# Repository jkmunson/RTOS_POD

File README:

BEGINNING OF NOTES BY WYATT:
3/10/2024

* TFT display guide: https://www.youtube.com/watch?v=3qnB5gsp8eE&t=2s
* SD card guide: https://01001000.xyz/2020-08-09-Tutorial-STM32CubeIDE-SD-card/
* All the SPI and GPIO pin assignments are made in the .ioc file.
* SCK, MISO, and MOSI are automaticly assigned by the SPI enabled in the .ioc
* ^ but CS, RESET, and DC need to be assigned manually.
* The ili9341.h file and main.h file will need to reflect the .ioc file pin assignments. 
* I used stack size = 512 for the display/SD thread. Testing lower values has caused a fault in the past.
* Will need to change the "startup file" from f4xxxx to whichever board we are using.
* None of the display's touch screen pins are used (i.e. T_IRQ1, T_DO, T_DIN, T_CS, T_CLK)

I was on an f4xxx board, but I used the following SPI/GPIOs for the SD/Display:
SD:
	SCK		->	PB10
	MISO	->	PC2
	MOSI	->	PC1
	CS		->	PC3
DISPLAY:
	SD0 (MISO)	->	n/a (specify master only transmit in .ioc)
	LED			->	+3.3V
	SCK			->	PA5
	SDI	(MOSI)	->	PA7
	DC			->	PB1
	RESET		->	PB0
	CS			->	PA4
	VCC			->  +5V
	
I uploaded my wyatt.c and wyatt.h code, but it doesn't look like main.c is configured for FreeRTOS to run.
Once it is, ADD THE FOLLOWING CODE AS ITS OWN THREAD:
  
*   HOW THE FSM WORKS:
	The display initializes by showing the names of the files on the SD card, and blinking to show which file is currently hovered over.
	Change boolean variables "sel_next" and "sel_prev" to highlight files other than the one currently highlighted.
	change boolean variable "readFile" to open the file that's currently hovered over and access its contents.
	change boolean variable "viewDirectory" to close the file you're reading and view the list of file names again.
	
	changing "readFile" while already reading a file does nothing.
	changing "viewDirectory" while already viewing the directory does nothing.
	
END OF NOTES BY WYATT.

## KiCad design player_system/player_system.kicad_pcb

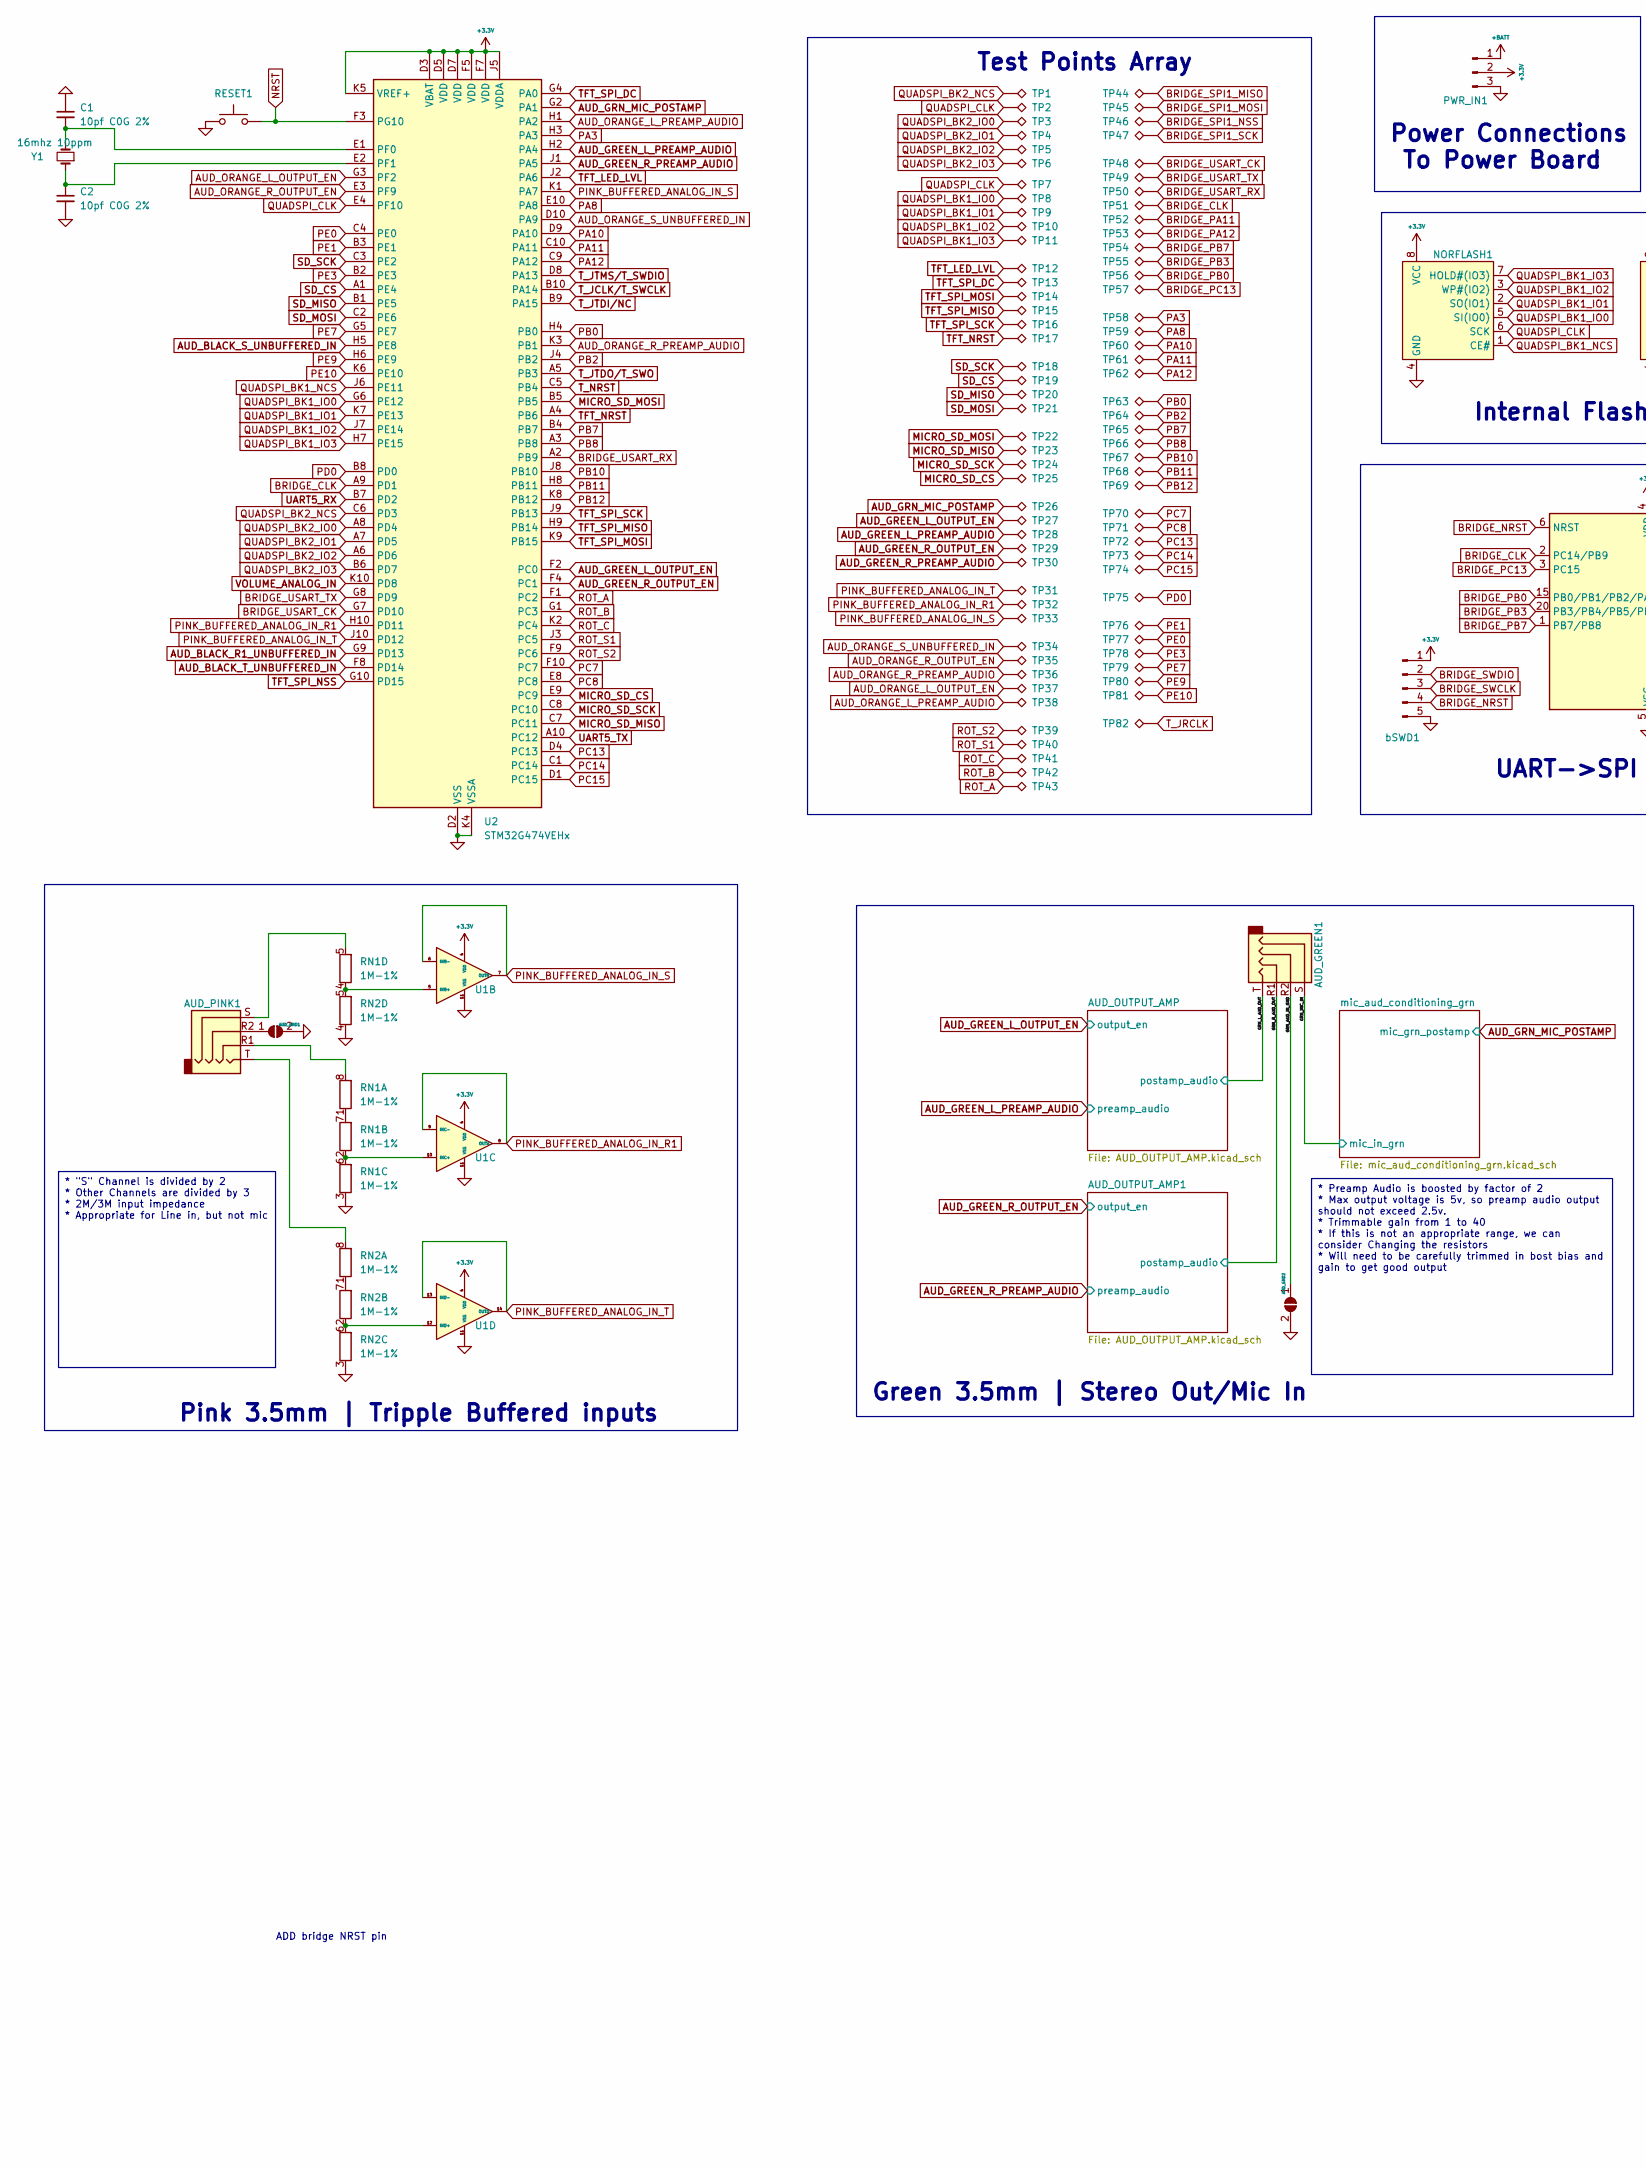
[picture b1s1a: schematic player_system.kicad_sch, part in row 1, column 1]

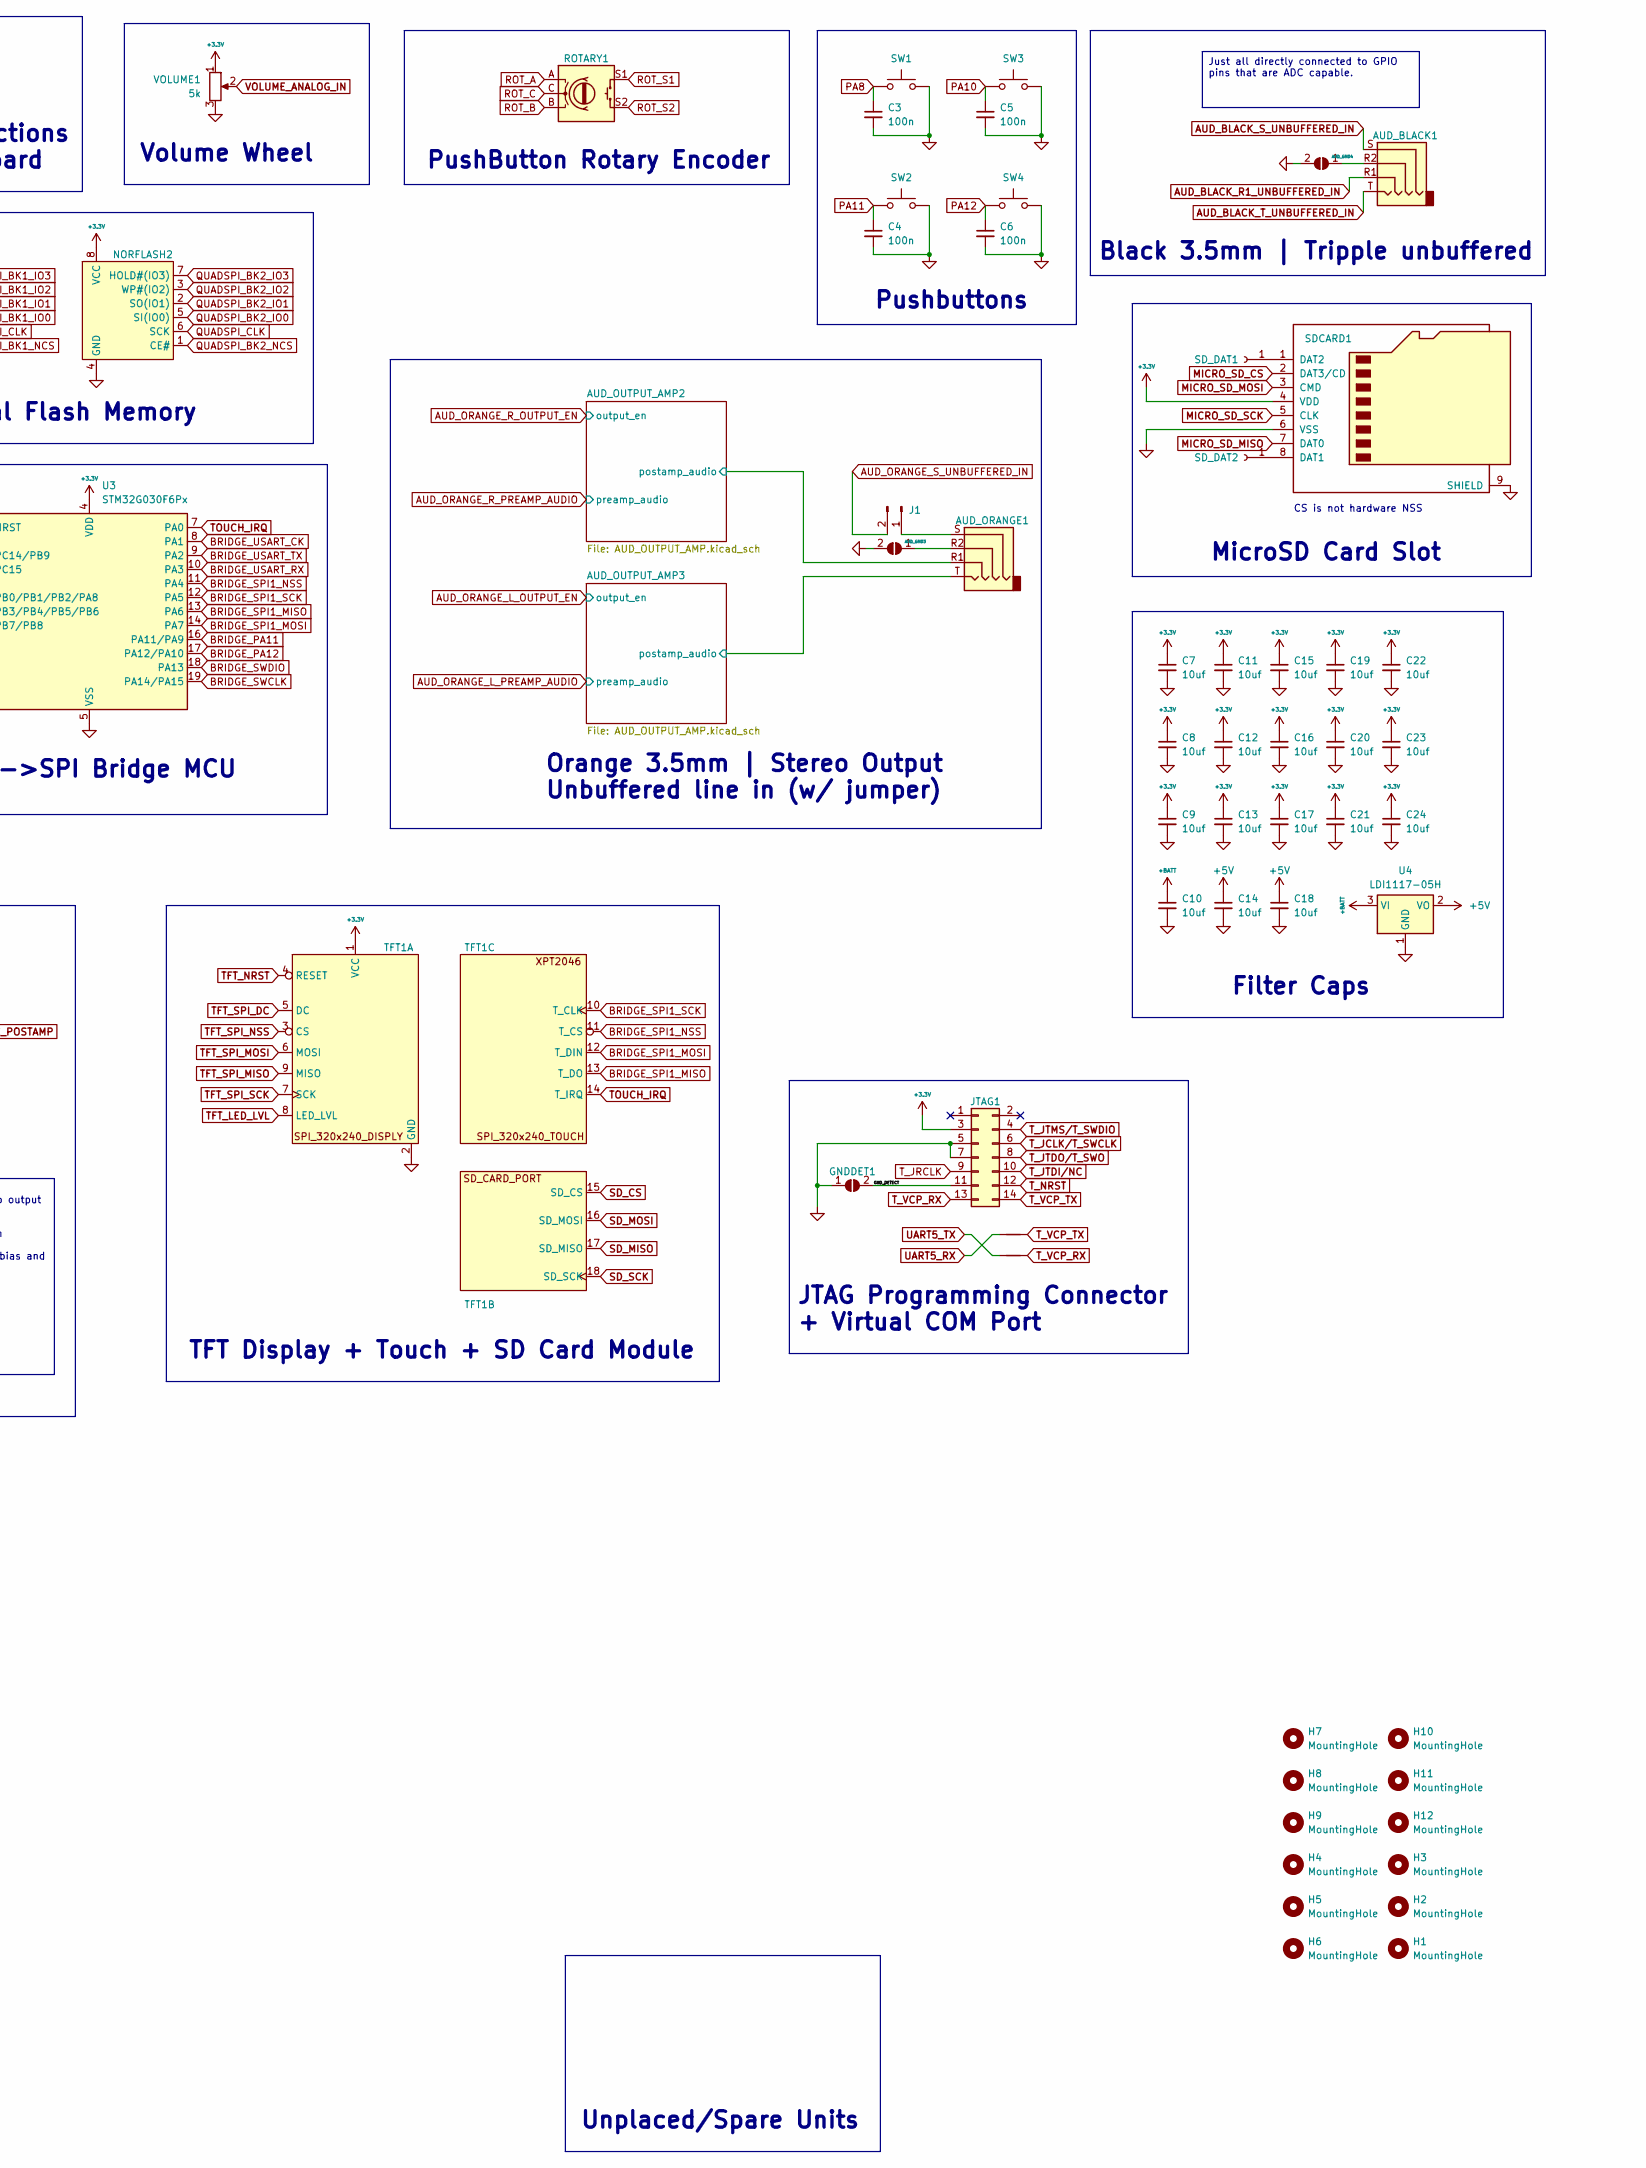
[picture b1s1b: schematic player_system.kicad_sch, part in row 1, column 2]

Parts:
AUD_BLACK1: TRRS_JACK_3.5mm
AUD_GND1, AUD_GND2, AUD_GND3, AUD_GND4: SolderJumper_2_Open; SolderJumper-2_P1.3mm_Open_RoundedPad1.0x1.5mm
AUD_GREEN1: TRRS_JACK_3.5mm
AUD_ORANGE1: TRRS_JACK_3.5mm
AUD_PINK1: TRRS_JACK_3.5mm
C1, C2: 10pf C0G 2%; C_0805_2012Metric_Pad1.18x1.45mm_HandSolder
C3, C4, C5, C6: 100n; C_0805_2012Metric_Pad1.18x1.45mm_HandSolder
C7, C8, C9, C10, C11, C12, C13, C14, C15, C16, C17, C18, C19, C20, C21, C22, C23, C24: 10uf; C_0805_2012Metric_Pad1.18x1.45mm_HandSolder
GNDDET1: SolderJumper_2_Open; SolderJumper-2_P1.3mm_Open_RoundedPad1.0x1.5mm
H1, H2, H3, H4, H5, H6, H7, H8, H9, H10, H11, H12: MountingHole; MountingHole_2.2mm_M2
J1: PinHeader_1x02_P2.54mm_Vertical
JTAG1: PGM; PinHeader_2x07_P1.27mm_Vertical
NORFLASH1, NORFLASH2: SOP-8_5.28x5.23mm_P1.27mm
NT2, NT3: NetTie_2; NetTie-2_SMD_Pad0.5mm
PWR_IN1: PinHeader_1x03_P2.54mm_Vertical
RESET1: RESET; SW_SPST_EVPBF
RN1, RN2: 1M-1%; R_Array_Convex_4x1206
ROTARY1: RotaryEncoder_Alps_EC11E-Switch_Vertical_H20mm_CircularMoun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
SDCARD1: J_SD_Card-micro_socket_A
SD_DAT1, SD_DAT2: .; tht_testpt
SW1, SW2, SW3, SW4: SW_SPST_EVPBF
TFT1: TFT_SPI_240X320
TP1, TP2, TP3, TP4, TP5, TP6, TP7, TP8, TP9, TP10, TP11, TP12, TP13, TP14, TP15, TP16, TP17, TP18, TP19, TP20, TP21, TP22, TP23, TP24, TP25, TP26, TP27, TP28, TP29, TP30, TP31, TP32, TP33, TP34, TP35, TP36, TP37, TP38, TP39, TP40, TP41, TP42, TP43, TP44, TP45, TP46, TP47, TP48, TP49, TP50, TP51, TP52, TP53, TP54, TP55, TP56, TP57, TP58, TP59, TP60, TP61, TP62, TP63, TP64, TP65, TP66, TP67, TP68, TP69, TP70, TP71, TP72, TP73, TP74, TP75, TP76, TP77, TP78, TP79, TP80, TP81, TP82: tht_testpt
U1: SOIC-14_3.9x8.7mm_P1.27mm
U2: STM32G474VEHx; TFBGA-100_8x8mm_Layout10x10_P0.8mm
U3: STM32G030F6Px; TSSOP-20_4.4x6.5mm_P0.65mm
U4: LDI1117-05H; SOT-223-3_TabPin2
VOLUME1: 5k; CIRCULAR_POT
Y1: 16mhz 10ppm; Crystal_SMD_2520-4Pin_2.5x2.0mm
bSWD1: BRIDGE_SWD; PinHeader_1x05_P2.54mm_Vertical

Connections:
+3.3V: C7.1, C8.1, C9.1, C11.1, C12.1, C13.1, C15.1, C16.1, C17.1, C19.1, C20.1, C21.1, C22.1, C23.1, C24.1, JTAG1.3, NORFLASH1.8 (VCC), NORFLASH2.8 (VCC), PWR_IN1.2, SDCARD1.4 (VDD), TFT1.1 (VCC), U1.4 (VDD), U2.D3 (VBAT), U2.D5 (VDD), U2.D7 (VDD), U2.F5 (VDD), U2.F7 (VDD), U2.J5 (VDDA), U2.K5 (VREF+), U3.4 (VDD), VOLUME1.1, bSWD1.1; also elsewhere on the board
+5V: C14.1, C18.1, U4.2 (VO); also elsewhere on the board
+BATT: C10.1, PWR_IN1.1, U4.3 (VI); also elsewhere on the board
/AUD_OUTPUT_AMP2/postamp_audio: AUD_ORANGE1.R1; also elsewhere on the board
/AUD_OUTPUT_AMP3/postamp_audio: AUD_ORANGE1.T; also elsewhere on the board
/GND_DETECT: GNDDET1.2 (B), JTAG1.11
/GRN_AUD_IN_GND: AUD_GND2.1 (A), AUD_GREEN1.R2
/GRN_L_AUD_OUT: AUD_GREEN1.T; also elsewhere on the board
/GRN_MIC_IN: AUD_GREEN1.S; also elsewhere on the board
/GRN_R_AUD_OUT: AUD_GREEN1.R1; also elsewhere on the board
AUD_BLACK_R1_UNBUFFERED_IN: AUD_BLACK1.R1, U2.G9 (PD13)
AUD_BLACK_S_UNBUFFERED_IN: AUD_BLACK1.S, U2.H5 (PE8)
AUD_BLACK_T_UNBUFFERED_IN: AUD_BLACK1.T, U2.F8 (PD14)
AUD_GREEN_L_OUTPUT_EN: TP27.1, U2.F2 (PC0); also elsewhere on the board
AUD_GREEN_L_PREAMP_AUDIO: TP28.1, U2.H2 (PA4); also elsewhere on the board
AUD_GREEN_R_OUTPUT_EN: TP29.1, U2.F4 (PC1); also elsewhere on the board
AUD_GREEN_R_PREAMP_AUDIO: TP30.1, U2.J1 (PA5); also elsewhere on the board
AUD_GRN_MIC_POSTAMP: TP26.1, U2.G2 (PA1); also elsewhere on the board
AUD_ORANGE_L_OUTPUT_EN: TP37.1, U2.G3 (PF2); also elsewhere on the board
AUD_ORANGE_L_PREAMP_AUDIO: TP38.1, U2.H1 (PA2); also elsewhere on the board
AUD_ORANGE_R_OUTPUT_EN: TP35.1, U2.E3 (PF9); also elsewhere on the board
AUD_ORANGE_R_PREAMP_AUDIO: TP36.1, U2.K3 (PB1); also elsewhere on the board
AUD_ORANGE_S_UNBUFFERED_IN: J1.2, TP34.1, U2.D10 (PA9)
BRIDGE_CLK: TP51.1, U2.A9 (PD1), U3.2 (PC14/PB9)
BRIDGE_NRST: U3.6 (NRST), bSWD1.4
BRIDGE_PA11: TP52.1, U3.16 (PA11/PA9)
BRIDGE_PA12: TP53.1, U3.17 (PA12/PA10)
BRIDGE_PB0: TP56.1, U3.15 (PB0/PB1/PB2/PA8)
BRIDGE_PB3: TP55.1, U3.20 (PB3/PB4/PB5/PB6)
BRIDGE_PB7: TP54.1, U3.1 (PB7/PB8)
BRIDGE_PC13: TP57.1, U3.3 (PC15)
BRIDGE_SPI1_MISO: TFT1.13 (T_DO), TP44.1, U3.13 (PA6)
BRIDGE_SPI1_MOSI: TFT1.12 (T_DIN), TP45.1, U3.14 (PA7)
BRIDGE_SPI1_NSS: TFT1.11 (T_CS), TP46.1, U3.11 (PA4)
BRIDGE_SPI1_SCK: TFT1.10 (T_CLK), TP47.1, U3.12 (PA5)
BRIDGE_SWCLK: U3.19 (PA14/PA15), bSWD1.3
BRIDGE_SWDIO: U3.18 (PA13), bSWD1.2
BRIDGE_USART_CK: TP48.1, U2.G7 (PD10), U3.8 (PA1)
BRIDGE_USART_RX: TP50.1, U2.A2 (PB9), U3.10 (PA3)
BRIDGE_USART_TX: TP49.1, U2.G8 (PD9), U3.9 (PA2)
GND: AUD_GND1.2 (B), AUD_GND2.2 (B), AUD_GND3.2 (B), AUD_GND4.2 (B), C1.1, C2.2, C3.2, C4.2, C5.2, C6.2, C7.2, C8.2, C9.2, C10.2, C11.2, C12.2, C13.2, C14.2, C15.2, C16.2, C17.2, C18.2, C19.2, C20.2, C21.2, C22.2, C23.2, C24.2, GNDDET1.1 (A), JTAG1.5, JTAG1.7, NORFLASH1.4 (GND), NORFLASH2.4 (GND), PWR_IN1.3, RESET1.1, RN1.3 (R3.1), RN2.3 (R3.1), RN2.4 (R4.1), SDCARD1.6 (VSS), SDCARD1.9 (SHIELD), SW1.2, SW2.2, SW3.2, SW4.2, TFT1.2 (GND), U1.11 (VSS), U2.D2 (VSS), U2.D6 (VSS), U2.E5 (VSS), U2.E6 (VSS), U2.E7 (VSS), U2.F6 (VSS), U2.K4 (VSSA), U3.5 (VSS), U4.1 (GND), VOLUME1.3, bSWD1.5; also elsewhere on the board
MICRO_SD_CS: SDCARD1.2 (DAT3/CD), TP25.1, U2.E9 (PC9)
MICRO_SD_MISO: SDCARD1.7 (DAT0), TP23.1, U2.C7 (PC11)
MICRO_SD_MOSI: SDCARD1.3 (CMD), TP22.1, U2.B5
MICRO_SD_SCK: SDCARD1.5 (CLK), TP24.1, U2.C8 (PC10)
NRST: RESET1.2, U2.F3 (PG10)
unnamed: AUD_GND1.1 (A), AUD_PINK1.R2
unnamed: AUD_GND3.1 (A), AUD_ORANGE1.R2
unnamed: AUD_BLACK1.R2, AUD_GND4.1 (A)
unnamed: AUD_ORANGE1.S, J1.1
unnamed: RN1.1 (R1.1), RN1.7 (R2.2)
unnamed: AUD_PINK1.R1, RN1.8 (R1.2)
unnamed: RN1.2 (R2.1), RN1.6 (R3.2), U1.10 (INC+)
unnamed: RN1.4 (R4.1), RN2.5 (R4.2), U1.5 (INB+)
unnamed: AUD_PINK1.S, RN1.5 (R4.2)
unnamed: RN2.1 (R1.1), RN2.7 (R2.2)
unnamed: AUD_PINK1.T, RN2.8 (R1.2)
unnamed: RN2.2 (R2.1), RN2.6 (R3.2), U1.12 (IND+)
unnamed: SDCARD1.8 (DAT1), SD_DAT2.1
unnamed: SDCARD1.1 (DAT2), SD_DAT1.1
unnamed: C1.2, U2.E1 (PF0), Y1.2, Y1.3 (2)
unnamed: C2.1, U2.E2 (PF1), Y1.1, Y1.4 (1)
PA3: TP58.1, U2.H3 (PA3)
PA8: C3.1, SW1.1, TP59.1, U2.E10 (PA8)
PA10: C5.1, SW3.1, TP60.1, U2.D9 (PA10)
PA11: C4.1, SW2.1, TP61.1, U2.C10 (PA11)
PA12: C6.1, SW4.1, TP62.1, U2.C9 (PA12)
PB0: TP63.1, U2.H4 (PB0)
PB2: TP64.1, U2.J4 (PB2)
PB7: TP65.1, U2.B4 (PB7)
PB8: TP66.1, U2.A3 (PB8)
PB10: TP67.1, U2.J8 (PB10)
PB11: TP68.1, U2.H8 (PB11)
PB12: TP69.1, U2.K8 (PB12)
PC7: TP70.1, U2.F10 (PC7)
PC8: TP71.1, U2.E8 (PC8)
PC13: TP72.1, U2.D4 (PC13)
PC14: TP73.1, U2.C1 (PC14)
PC15: TP74.1, U2.D1 (PC15)
PD0: TP75.1, U2.B8 (PD0)
PE0: TP77.1, U2.C4 (PE0)
PE1: TP76.1, U2.B3 (PE1)
PE3: TP78.1, U2.B2 (PE3)
PE7: TP79.1, U2.G5 (PE7)
PE9: TP80.1, U2.H6 (PE9)
PE10: TP81.1, U2.K6 (PE10)
PINK_BUFFERED_ANALOG_IN_R1: TP32.1, U1.8 (OUTA), U1.9 (INC-), U2.H10 (PD11)
PINK_BUFFERED_ANALOG_IN_S: TP33.1, U1.6 (INB-), U1.7 (OUTB), U2.K1 (PA7)
PINK_BUFFERED_ANALOG_IN_T: TP31.1, U1.13 (IND-), U1.14 (OUTD), U2.J10 (PD12)
QUADSPI_BK1_IO0: NORFLASH1.5 (SI(IO0)), TP8.1, U2.G6 (PE12)
QUADSPI_BK1_IO1: NORFLASH1.2 (SO(IO1)), TP9.1, U2.K7 (PE13)
QUADSPI_BK1_IO2: NORFLASH1.3 (WP#(IO2)), TP10.1, U2.J7 (PE14)
QUADSPI_BK1_IO3: NORFLASH1.7 (HOLD#(IO3)), TP11.1, U2.H7 (PE15)
QUADSPI_BK1_NCS: NORFLASH1.1 (CE#), U2.J6 (PE11)
QUADSPI_BK2_IO0: NORFLASH2.5 (SI(IO0)), TP3.1, U2.A8 (PD4)
QUADSPI_BK2_IO1: NORFLASH2.2 (SO(IO1)), TP4.1, U2.A7 (PD5)
QUADSPI_BK2_IO2: NORFLASH2.3 (WP#(IO2)), TP5.1, U2.A6 (PD6)
QUADSPI_BK2_IO3: NORFLASH2.7 (HOLD#(IO3)), TP6.1, U2.B6 (PD7)
QUADSPI_BK2_NCS: NORFLASH2.1 (CE#), TP1.1, U2.C6 (PD3)
QUADSPI_CLK: NORFLASH1.6 (SCK), NORFLASH2.6 (SCK), TP2.1, TP7.1, U2.E4 (PF10)
ROT_A: ROTARY1.A, TP43.1, U2.F1 (PC2)
ROT_B: ROTARY1.B, TP42.1, U2.G1 (PC3)
ROT_C: ROTARY1.C, TP41.1, U2.K2 (PC4)
ROT_S1: ROTARY1.S1, TP40.1, U2.J3 (PC5)
ROT_S2: ROTARY1.S2, TP39.1, U2.F9 (PC6)
SD_CS: TFT1.15 (SD_CS), TP19.1, U2.A1 (PE4)
SD_MISO: TFT1.17 (SD_MISO), TP20.1, U2.B1 (PE5)
SD_MOSI: TFT1.16 (SD_MOSI), TP21.1, U2.C2 (PE6)
SD_SCK: TFT1.18 (SD_SCK), TP18.1, U2.C3 (PE2)
TFT_LED_LVL: TFT1.8 (LED_LVL), TP12.1, U2.J2 (PA6)
TFT_NRST: TFT1.4 (RESET), TP17.1, U2.A4 (PB6)
TFT_SPI_DC: TFT1.5 (DC), TP13.1, U2.G4 (PA0)
TFT_SPI_MISO: TFT1.9 (MISO), TP15.1, U2.H9 (PB14)
TFT_SPI_MOSI: TFT1.6 (MOSI), TP14.1, U2.K9 (PB15)
TFT_SPI_NSS: TFT1.3 (CS), U2.G10 (PD15)
TFT_SPI_SCK: TFT1.7 (SCK), TP16.1, U2.J9 (PB13)
TOUCH_IRQ: TFT1.14 (T_IRQ), U3.7 (PA0)
T_JCLK/T_SWCLK: JTAG1.6, U2.B10 (PA14)
T_JRCLK: JTAG1.9, TP82.1
T_JTDI/NC: JTAG1.10, U2.B9 (PA15)
T_JTDO/T_SWO: JTAG1.8, U2.A5 (PB3)
T_JTMS/T_SWDIO: JTAG1.4, U2.D8 (PA13)
T_NRST: JTAG1.12, U2.C5 (PB4)
T_VCP_RX: JTAG1.13, NT3.2
T_VCP_TX: JTAG1.14, NT2.2
UART5_RX: NT2.1, U2.B7 (PD2)
UART5_TX: NT3.1, U2.A10 (PC12)
VOLUME_ANALOG_IN: U2.K10 (PD8), VOLUME1.2

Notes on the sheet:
* "S" Channel is divided by 2 * Other Channels are divided by 3 * 2M/3M input impedance * Appropriate for Line in, but not mic
* Preamp Audio is boosted by factor of 2 * Max output voltage is 5v, so preamp audio output should not exceed 2.5v. * Trimmable gain from 1 to 40 * If this is not an appropriate range, we can consider Changing the resistors * Will need to be carefully trimmed in bost bias and gain to get good output
Just all directly connected to GPIO pins that are ADC capable.
MicroSD Card Slot
JTAG Programming Connector + Virtual COM Port
CS is not hardware NSS
Unplaced/Spare Units
Power Connections To Power Board
Orange 3.5mm | Stereo Output Unbuffered line in (w/ jumper)
Black 3.5mm | Tripple unbuffered
TFT Display + Touch + SD Card Module
ADD bridge NRST pin
Volume Wheel
Pink 3.5mm | Tripple Buffered inputs
Test Points Array
Pushbuttons
Filter Caps
Green 3.5mm | Stereo Out/Mic In
Internal Flash Memory
UART->SPI Bridge MCU
PushButton Rotary Encoder

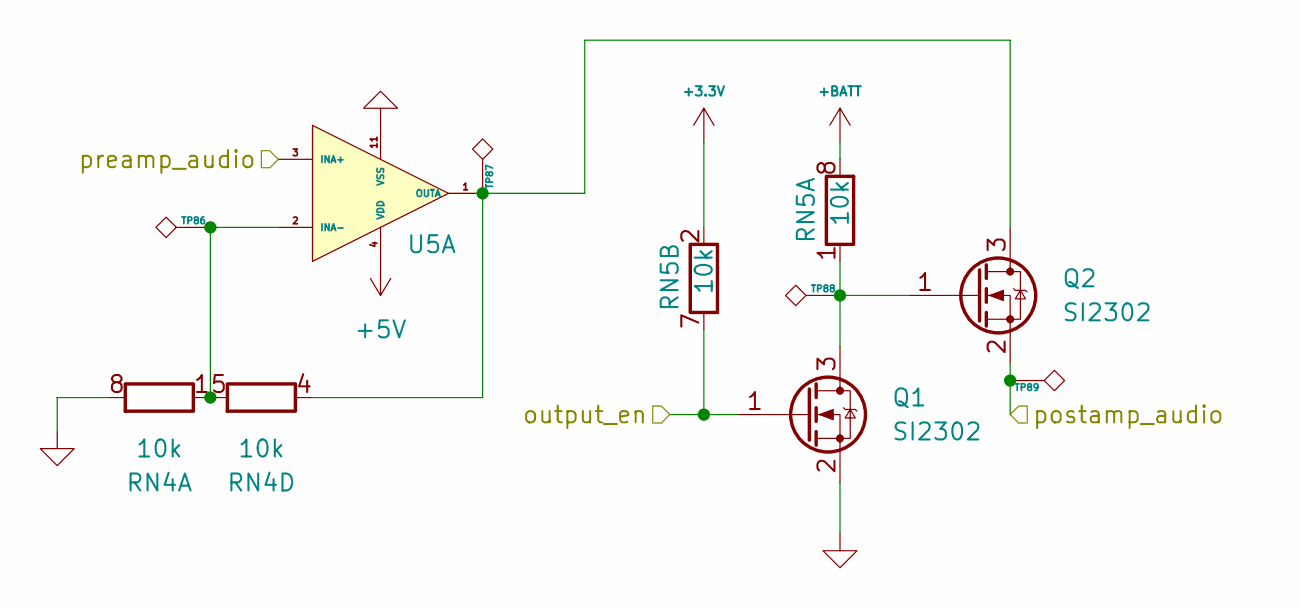
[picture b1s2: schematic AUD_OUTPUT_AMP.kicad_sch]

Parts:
Q1, Q2: SI2302; SOT-23
RN4, RN5: 10k; R_Array_Concave_4x0603
TP86, TP87, TP88, TP89: tht_testpt
U5: SOIC-14_3.9x8.7mm_P1.27mm

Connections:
+3.3V: RN5.2 (R2.1), RN5.3 (R3.1); also elsewhere on the board
+5V: U5.4 (VDD); also elsewhere on the board
+BATT: RN5.5 (R4.2), RN5.8 (R1.2); also elsewhere on the board
/GRN_L_AUD_OUT: Q2.2 (S), TP89.1; also elsewhere on the board
AUD_GREEN_L_OUTPUT_EN: Q1.1 (G), RN5.7 (R2.2); also elsewhere on the board
AUD_GREEN_L_PREAMP_AUDIO: U5.3 (INA+); also elsewhere on the board
AUD_GREEN_R_OUTPUT_EN: RN5.6 (R3.2); also elsewhere on the board
AUD_GREEN_R_PREAMP_AUDIO: U5.5 (INB+); also elsewhere on the board
AUD_ORANGE_L_PREAMP_AUDIO: U5.10 (INC+); also elsewhere on the board
AUD_ORANGE_R_PREAMP_AUDIO: U5.12 (IND+); also elsewhere on the board
GND: Q1.2 (S), RN4.6 (R3.2), RN4.8 (R1.2), U5.11 (VSS); also elsewhere on the board
unnamed: Q1.3 (D), Q2.1 (G), RN5.1 (R1.1), TP88.1
unnamed: Q2.3 (D), RN4.4 (R4.1), TP87.1, U5.1 (OUTA)
unnamed 53: RN5.4 (R4.1); also elsewhere on the board
unnamed 54: RN4.2 (R2.1), U5.7 (OUTB); also elsewhere on the board
unnamed 56: U5.14 (OUTD); also elsewhere on the board
unnamed 58: U5.8 (OUTA); also elsewhere on the board
unnamed: RN4.1 (R1.1), RN4.5 (R4.2), TP86.1, U5.2 (INA-)
unnamed 69: RN4.3 (R3.1), RN4.7 (R2.2), U5.6 (INB-); also elsewhere on the board
unnamed 70: U5.13 (IND-); also elsewhere on the board
unnamed 71: U5.9 (INC-); also elsewhere on the board

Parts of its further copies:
Q3, Q4, Q5, Q6, Q7, Q8: SI2302; SOT-23
RN6, RN7: 10k; R_Array_Concave_4x0603
TP90, TP91, TP92, TP93, TP94, TP95, TP96, TP97, TP98, TP99, TP100, TP101: tht_testpt

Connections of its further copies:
+3.3V: RN6.1 (R1.1), RN6.4 (R4.1); also elsewhere on the board
+BATT: RN7.5 (R4.2), RN7.8 (R1.2); also elsewhere on the board
/AUD_OUTPUT_AMP2/postamp_audio: Q6.2 (S), TP97.1; also elsewhere on the board
/AUD_OUTPUT_AMP3/postamp_audio: Q8.2 (S), TP101.1; also elsewhere on the board
/GRN_R_AUD_OUT: Q4.2 (S), TP93.1; also elsewhere on the board
AUD_GREEN_R_OUTPUT_EN: Q3.1 (G); also elsewhere on the board
AUD_ORANGE_L_OUTPUT_EN: Q7.1 (G), RN6.8 (R1.2); also elsewhere on the board
AUD_ORANGE_R_OUTPUT_EN: Q5.1 (G), RN6.5 (R4.2); also elsewhere on the board
GND: Q3.2 (S), Q5.2 (S), Q7.2 (S), RN6.6 (R3.2), RN7.6 (R3.2); also elsewhere on the board
unnamed 53: Q3.3 (D), Q4.1 (G), TP92.1; also elsewhere on the board
unnamed 54: Q4.3 (D), TP91.1; also elsewhere on the board
unnamed: Q5.3 (D), Q6.1 (G), RN7.1 (R1.1), TP96.1
unnamed 56: Q6.3 (D), RN6.2 (R2.1), TP95.1; also elsewhere on the board
unnamed: Q7.3 (D), Q8.1 (G), RN7.4 (R4.1), TP100.1
unnamed 58: Q8.3 (D), RN7.2 (R2.1), TP99.1; also elsewhere on the board
unnamed 69: TP90.1; also elsewhere on the board
unnamed 70: RN6.3 (R3.1), RN6.7 (R2.2), TP94.1; also elsewhere on the board
unnamed 71: RN7.3 (R3.1), RN7.7 (R2.2), TP98.1; also elsewhere on the board

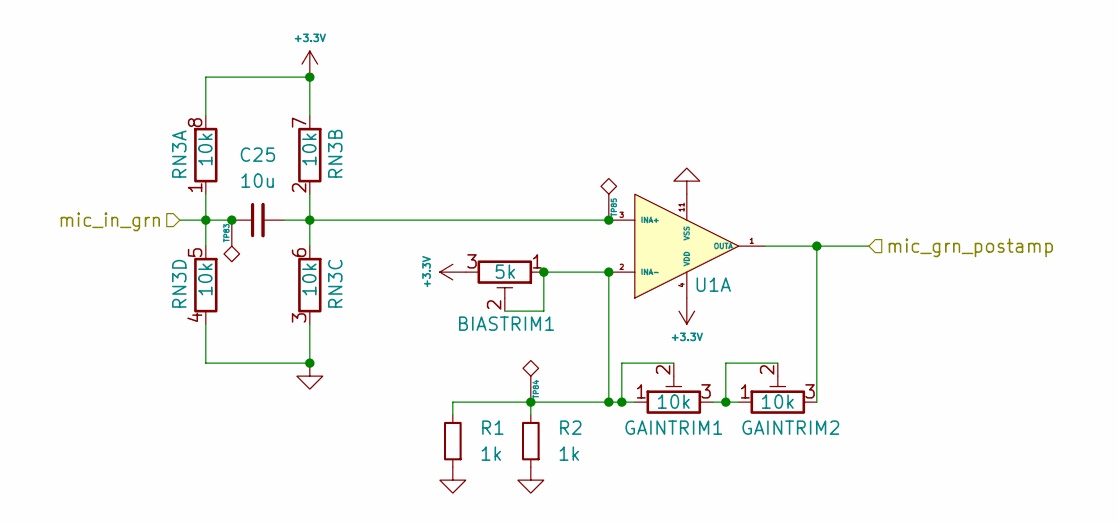
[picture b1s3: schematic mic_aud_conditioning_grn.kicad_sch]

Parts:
BIASTRIM1: 5k; Potentiometer_ACP_CA9-H5_Horizontal
C25: 10u; R_0805_2012Metric_Pad1.20x1.40mm_HandSolder
GAINTRIM1, GAINTRIM2: 10k; Potentiometer_ACP_CA9-H5_Horizontal
R1, R2: 1k; R_0805_2012Metric_Pad1.20x1.40mm_HandSolder
RN3: 10k; R_Array_Concave_4x0603
TP83, TP84, TP85: tht_testpt
U1: SOIC-14_3.9x8.7mm_P1.27mm

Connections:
+3.3V: BIASTRIM1.3, RN3.7 (R2.2), RN3.8 (R1.2), U1.4 (VDD); also elsewhere on the board
/GRN_MIC_IN: C25.1, RN3.1 (R1.1), RN3.5 (R4.2), TP83.1; also elsewhere on the board
AUD_GRN_MIC_POSTAMP: GAINTRIM2.3, U1.1 (OUTA); also elsewhere on the board
GND: R1.1, R2.1, RN3.3 (R3.1), RN3.4 (R4.1), U1.11 (VSS); also elsewhere on the board
unnamed: GAINTRIM1.3, GAINTRIM2.1, GAINTRIM2.2
unnamed: C25.2, RN3.2 (R2.1), RN3.6 (R3.2), TP85.1, U1.3 (INA+)
unnamed: BIASTRIM1.1, BIASTRIM1.2, GAINTRIM1.1, GAINTRIM1.2, R1.2, R2.2, TP84.1, U1.2 (INA-)

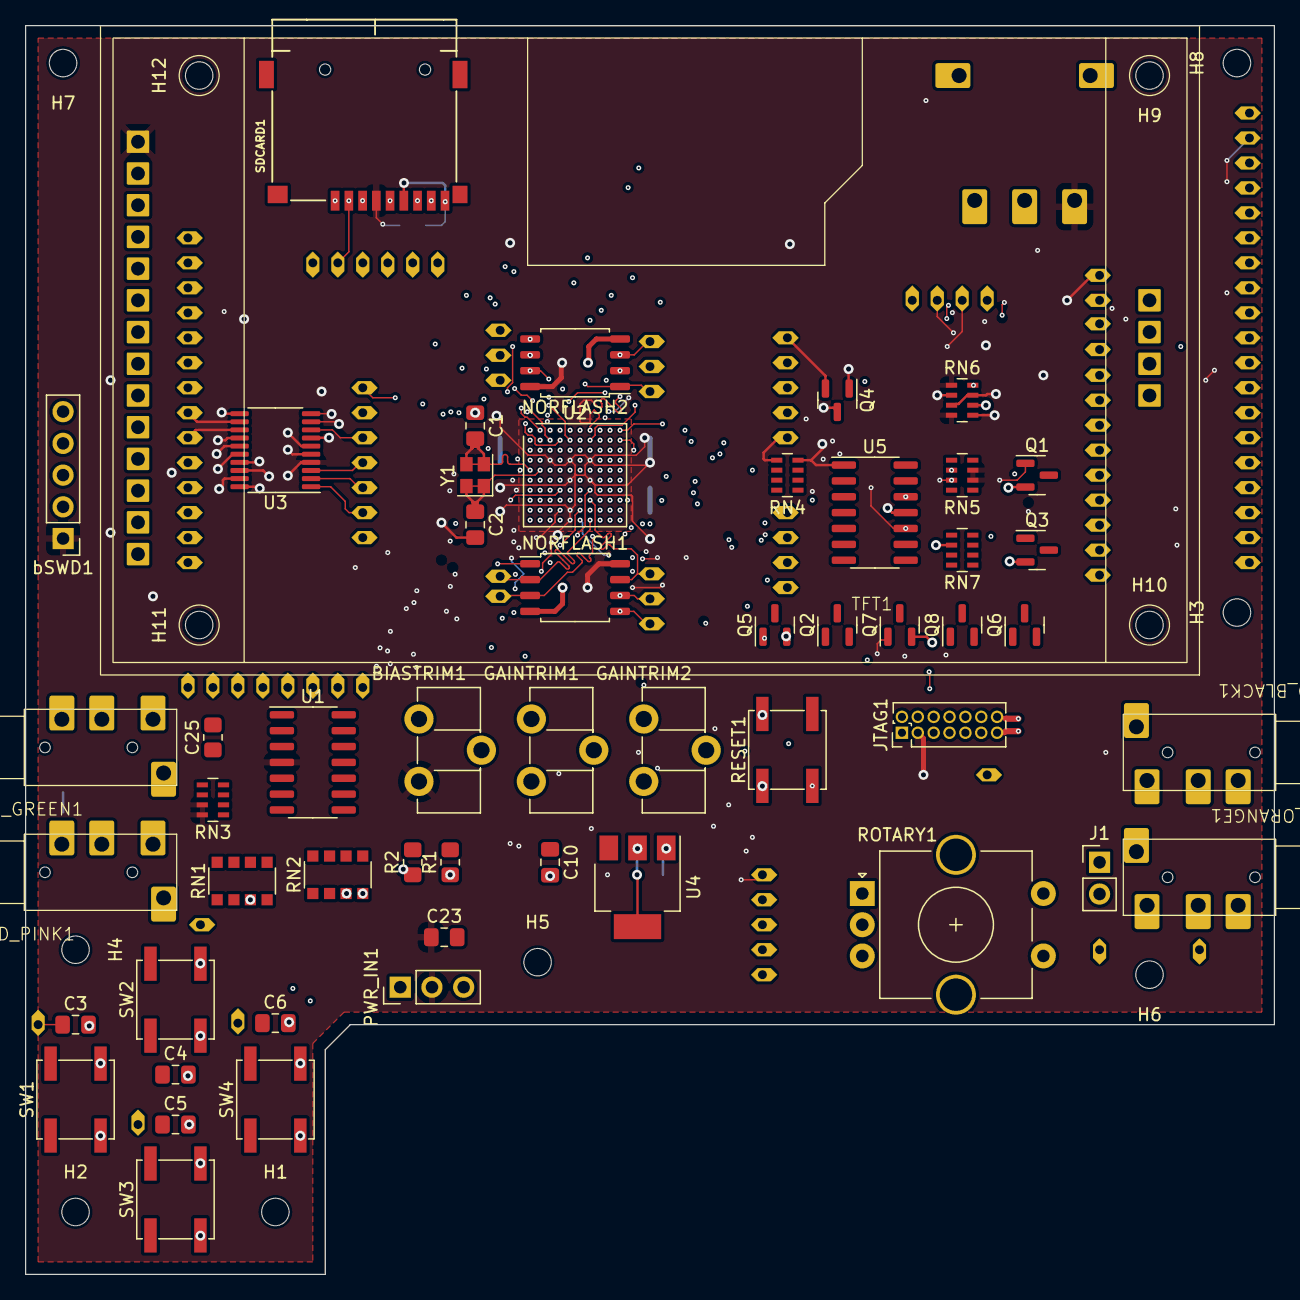
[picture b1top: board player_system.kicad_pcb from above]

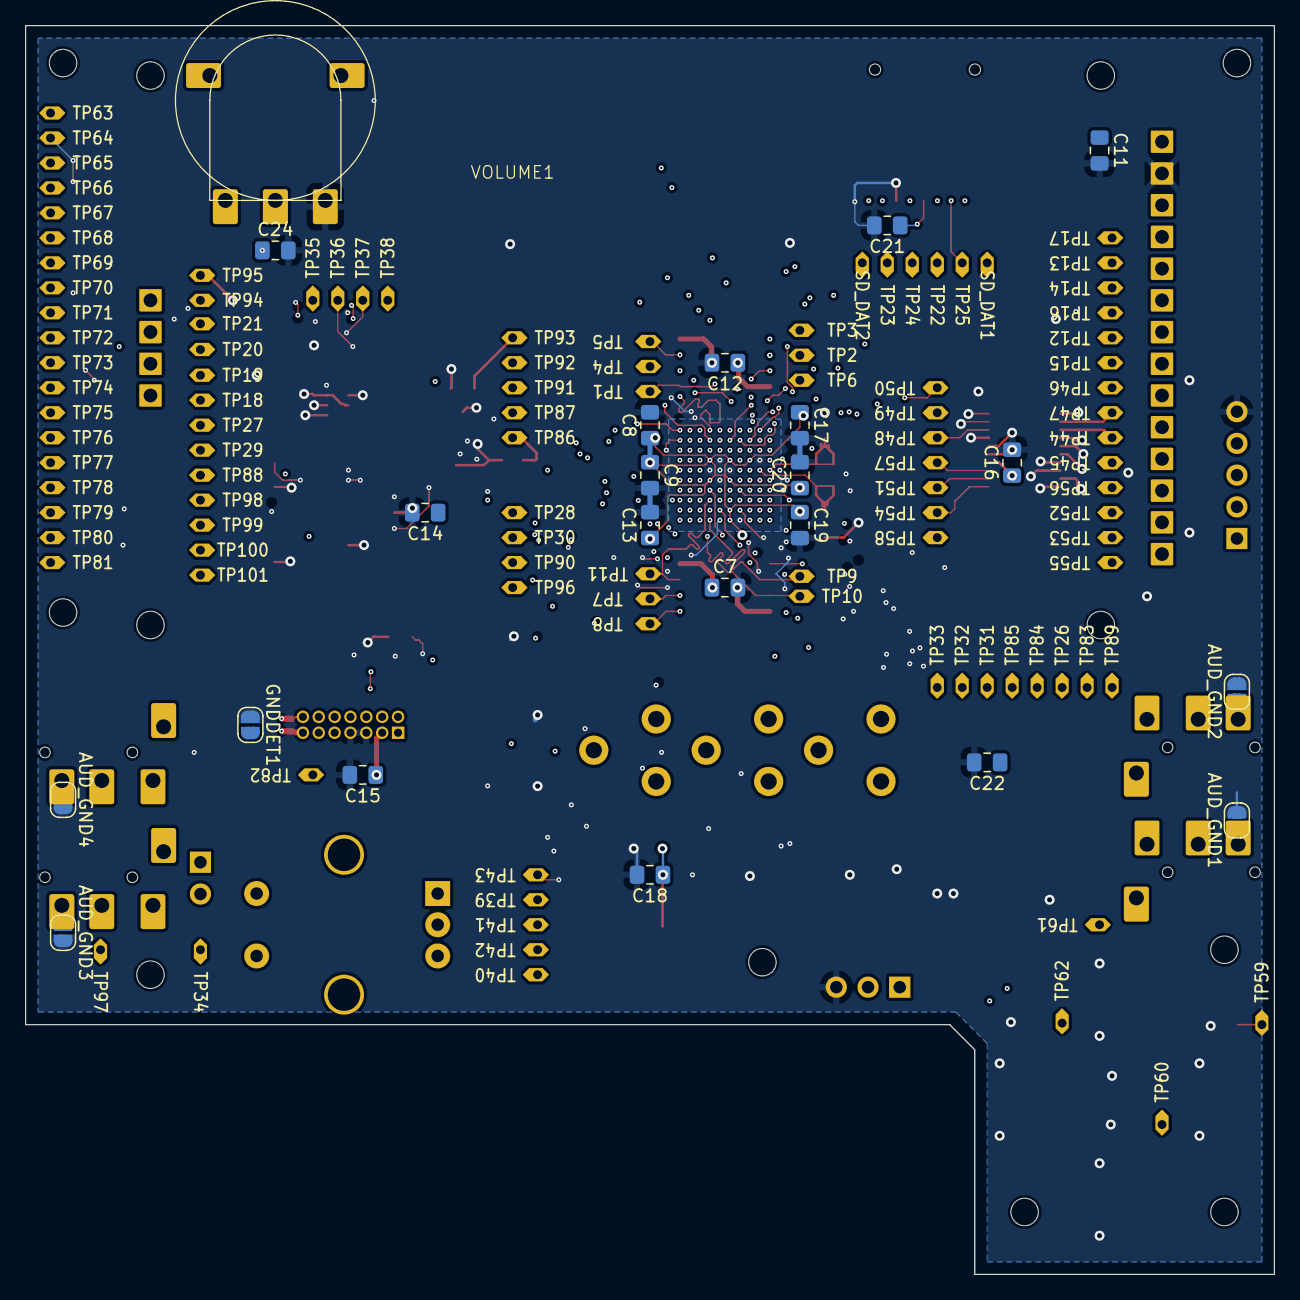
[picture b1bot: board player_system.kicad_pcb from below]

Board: 4 copper layers, 100.0 x 100.0 mm, 192 parts (125 on the bottom side), 143 nets.

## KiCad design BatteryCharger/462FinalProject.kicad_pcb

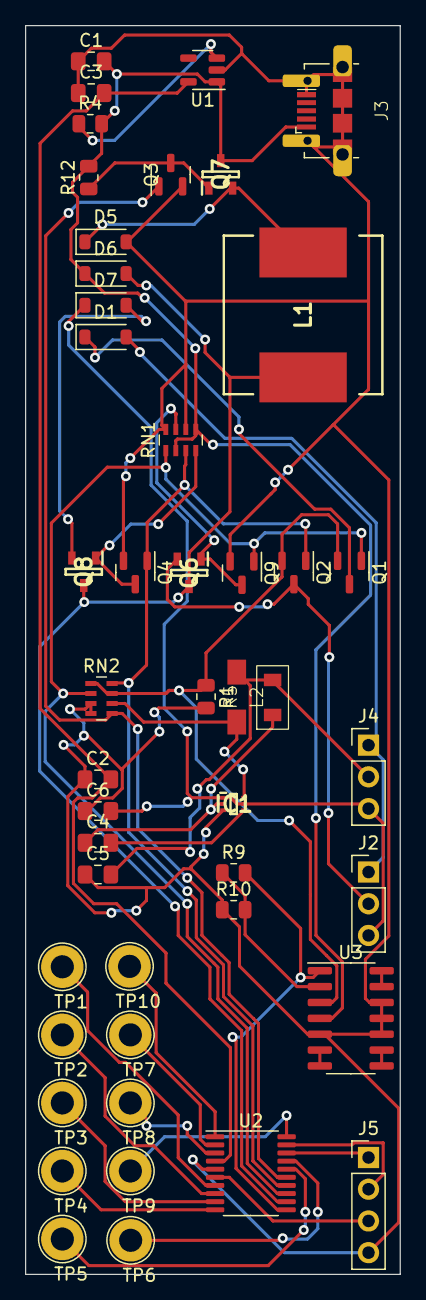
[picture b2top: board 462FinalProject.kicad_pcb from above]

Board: 2 copper layers, 30.0 x 100.0 mm, 46 parts (0 on the bottom side), 40 nets.

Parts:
C1, C2, C3, C5, C6: 10u; C_0805_2012Metric_Pad1.18x1.45mm_HandSolder
C4: .1u; C_0805_2012Metric_Pad1.18x1.45mm_HandSolder
D1, D5, D6, D7: MBR0530; D_SOD-123
IC1: TPS562231DRLR; SOTFL50P160X60-6N
J2: 3_Pin_Header_to_Battery; PinHeader_1x03_P2.54mm_Vertical
J3: USB_B_Micro; USB_Micro-B_roundholes
J4: 3_Pin_Header_to_IPOD; PinHeader_1x03_P2.54mm_Vertical
J5: Conn_01x04_Pin; PinHeader_1x04_P2.54mm_Vertical
L1: SRR1205-500YL; SRR1205500YL
L2: 3.3u; CC322522A-4R7K
Q1, Q2: MMFTN6001; SOT-23
Q3, Q4, Q9: SI2302; SOT-23
Q6, Q7, Q8: BSS84AK,215; SOT95P230X110-3N
R1: 100m; R_0805_2012Metric
R4, R10, R12: 1k; R_0805_2012Metric
R5: 45.3k; CR0603-FX-4532ELF
R9: 100k; R_0805_2012Metric
RN1, RN2: R_Pack04_Split_2; R_Array_Concave_4x0603
TP1, TP2, TP3, TP4, TP5, TP6, TP7, TP8, TP9, TP10: TestPoint; TestPoint_Loop_D2.50mm_Drill1.85mm
U1: MIC5504-3.3YM5; SOT-23-5
U2: STM32G030F6Px; TSSOP-20_4.4x6.5mm_P0.65mm
U3: SOIC-14_3.9x8.7mm_P1.27mm

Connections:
3.3v Battery: C5.2, J4.2, L2.2, R5.1
ADC_Current: R9.2, U2.11 (PA4), U3.1 (OUTA)
ADC_v-to-c: Q1.2 (S), Q2.2 (S), R1.1, RN2.1 (R1.1), RN2.7 (R2.2), U3.3 (INA+)
BST: C4.2, IC1.4 (BST)
FB: IC1.6 (FB), R5.2, RN2.6 (R3.2)
GND: C1.1, C2.1, C3.1, C5.1, C6.1, D5.2 (A), IC1.3 (GND), J3.5 (GND), J3.6 (Shield), J5.4, Q3.2 (S), Q4.2 (S), Q9.2 (S), R1.2, R10.1, RN1.6 (R3.2), RN1.8 (R1.2), RN2.3 (R3.1), RN2.4 (R4.1), U1.2 (GND), U2.5 (VSS), U3.5 (INB+), U3.10 (INC+), U3.11 (VSS), U3.12 (IND+)
LiPO1_Control: Q1.1 (G), Q9.1 (G), RN1.1 (R1.1), RN2.2 (R2.1), U2.13 (PA6)
LiPO2_Control: Q2.1 (G), Q4.1 (G), RN1.3 (R3.1), RN2.8 (R1.2), U2.14 (PA7)
LiPO High: C6.2, D7.1 (K), IC1.1 (VIN), IC1.5 (EN), J2.3, J4.3
LiPO Low: D1.2 (A), J2.1, J4.1
LiPO Mid: J2.2, Q2.3 (D), Q6.2 (S)
MCU Vdd: C2.2, C3.2, U1.5 (VOUT), U2.4 (VDD)
NRST: J5.3, U2.6 (NRST)
unnamed: D1.1 (K), Q1.3 (D)
unnamed: D5.1 (K), L1.1, Q7.2 (S)
unnamed: D7.2 (A), Q8.2 (S)
unnamed: Q3.3 (D), Q7.1 (G), R12.1
unnamed: Q4.3 (D), Q8.1 (G), RN1.4 (R4.1)
unnamed: Q6.1 (G), Q9.3 (D), RN1.7 (R2.2)
unnamed: R4.1, U1.3 (EN)
unnamed: R9.1, R10.2, U3.2 (INA-)
unnamed: U3.6 (INB-), U3.7 (OUTB)
unnamed: U3.8 (OUTA), U3.9 (INC-)
unnamed: U3.13 (IND-), U3.14 (OUTD)
PA0_MCU: TP1.1, U2.7 (PA0)
PA1_MCU: TP2.1, U2.8 (PA1)
PA2_MCU: TP3.1, U2.9 (PA2)
PA3_MCU: TP4.1, U2.10 (PA3)
PA11_PA9_MCU: TP5.1, U2.16 (PA11/PA9)
PA12_PA10_MCU: TP6.1, U2.17 (PA12/PA10)
PB3_PB4_PB5P_PB6_MCU: TP9.1, U2.20 (PB3/PB4/PB5/PB6)
PB7_PB8_MCU: TP10.1, U2.1 (PB7/PB8)
PC14_PB9_MCU: TP7.1, U2.2 (PC14/PB9)
PC15_MCU: TP8.1, U2.3 (PC15)
SW: C4.1, IC1.2 (SW), L2.1
SWCLK: J5.2, U2.19 (PA14/PA15)
SWDIO: J5.1, U2.18 (PA13)
Switch_Regulated_V: D6.2 (A), L1.2, Q6.3 (D), Q8.3 (D), U2.12 (PA5)
Switch_Regulator_PWM: Q3.1 (G), RN2.5 (R4.2), U2.15 (PB0/PB1/PB2/PA8)
USB Vdc: C1.2, D6.1 (K), J3.1 (VBUS), Q7.3 (D), R4.2, R12.2, RN1.2 (R2.1), RN1.5 (R4.2), U1.1 (VIN), U3.4 (VDD)
